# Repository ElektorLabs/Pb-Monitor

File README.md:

# Pb-Monitor

Pb-Monitor is a project developed by ElektorLabs aimed at monitoring lead-acid batteries. This repository contains both hardware schematics and firmware source code to facilitate the monitoring process.

## Features

- **Hardware Design**: Detailed schematics and design files for building the Pb-Monitor hardware.
- **Firmware**: Source code for the microcontroller to interface with the hardware and perform monitoring tasks.

## Repository Structure

- **hardware/**: Contains all hardware design files and schematics.
- **src/PbMonitor/**: Contains the firmware source code for the Pb-Monitor.

## Getting Started

To get started with Pb-Monitor:

1. **Clone the Repository**:
   ```bash
   git clone https://github.com/ElektorLabs/Pb-Monitor.git
   ```
2. **Explore the Hardware Design**:
   - Navigate to the `hardware/` directory to find schematics and design files.
3. **Build the Firmware**:
   - Navigate to the `src/PbMonitor/` directory.
   - Follow the build instructions provided in the source code to compile and upload the firmware to your microcontroller.

## License

This project is licensed under the GNU General Public License v3.0. For more details, refer to the [LICENSE](https://github.com/ElektorLabs/Pb-Monitor/blob/main/LICENSE) file.

## Contributing

Contributions are welcome! If you have suggestions or improvements, feel free to open an issue or submit a pull request.

## Contact

For more information or support, please contact ElektorLabs through their [GitHub profile](https://github.com/ElektorLabs).

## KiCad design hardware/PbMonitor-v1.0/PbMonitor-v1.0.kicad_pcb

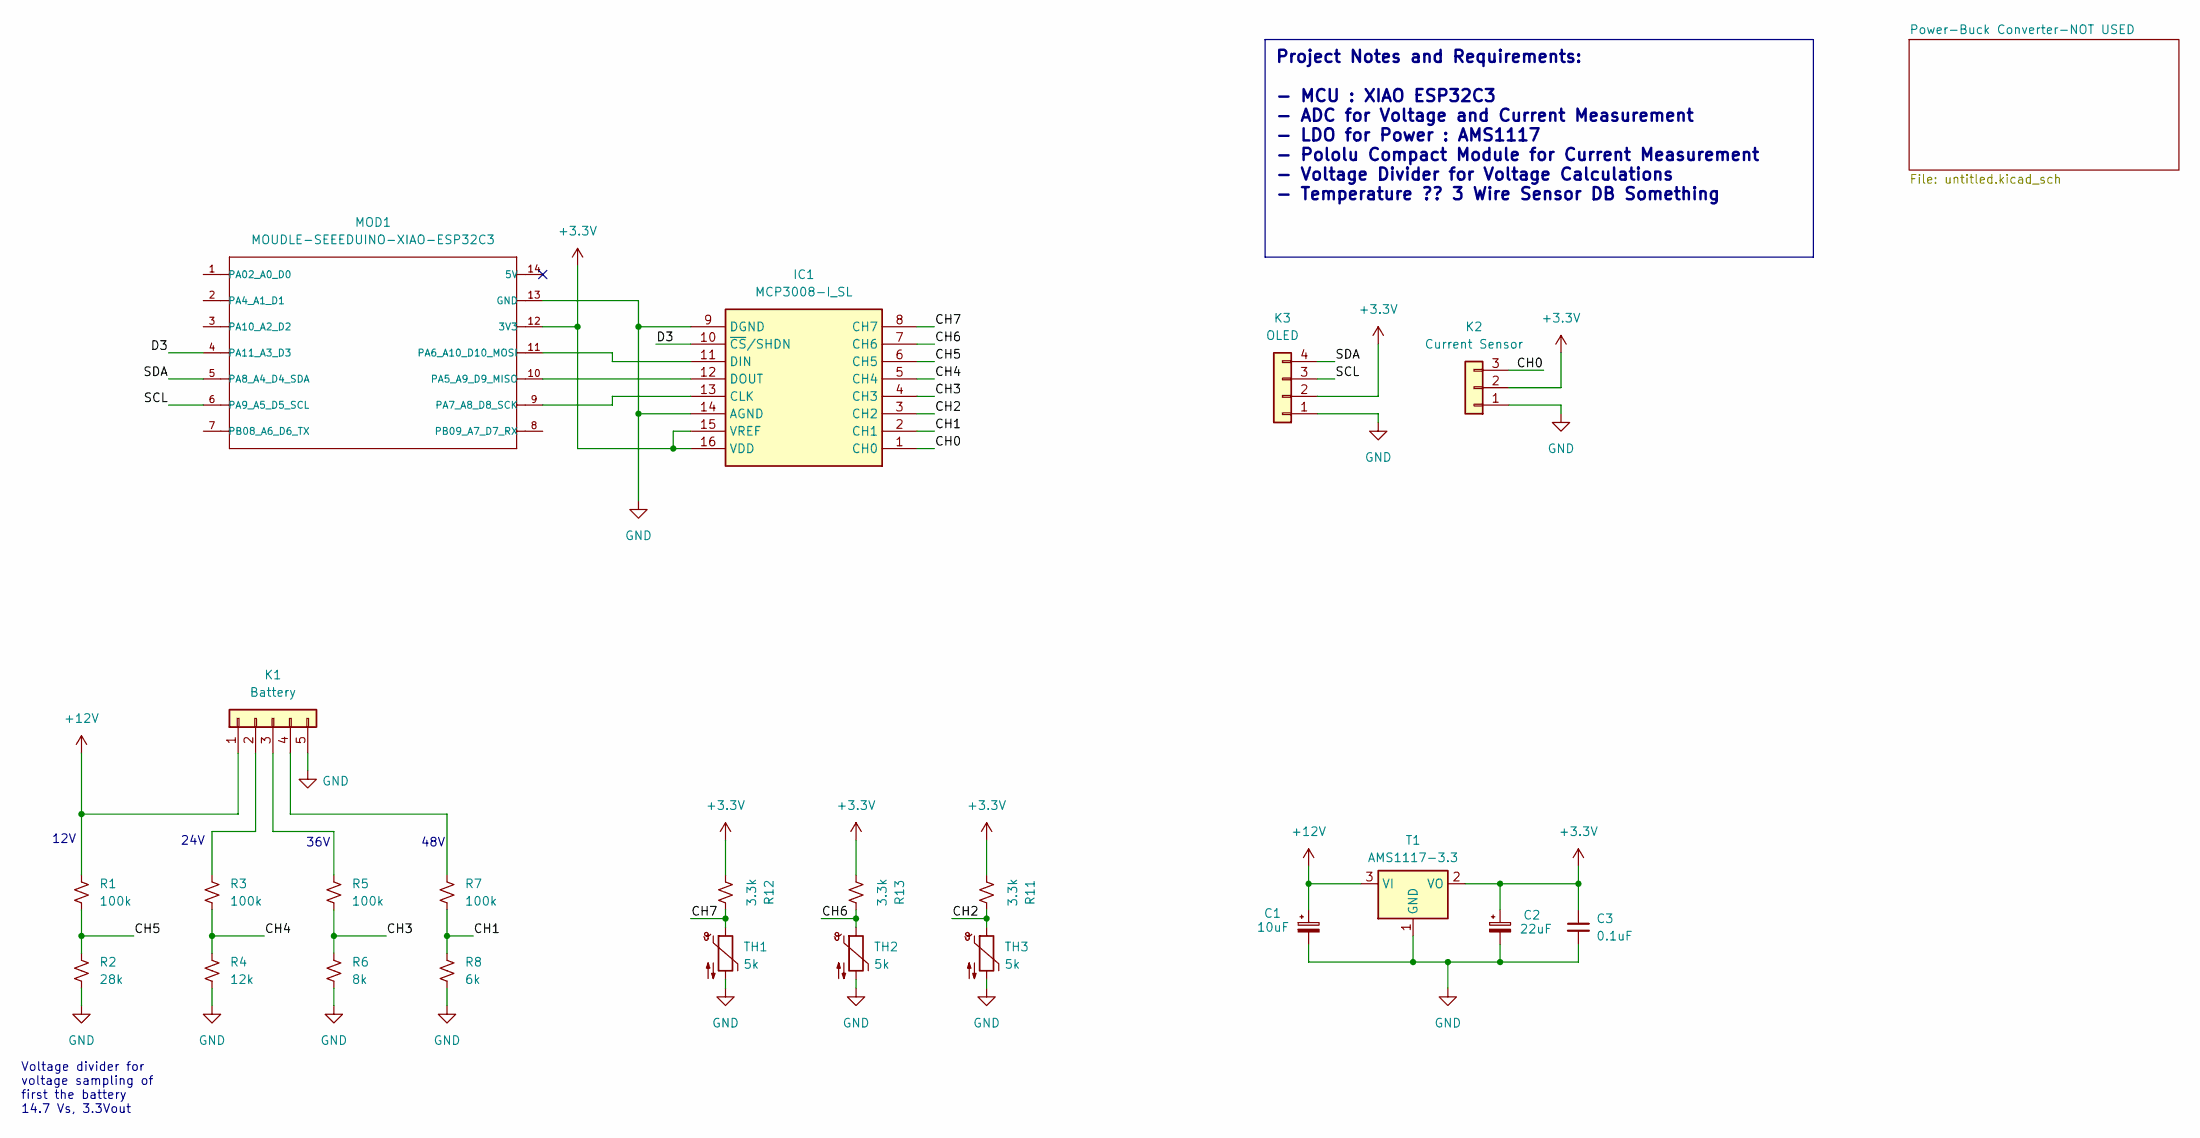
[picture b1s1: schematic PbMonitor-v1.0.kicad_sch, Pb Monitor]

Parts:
C1: 10uF; CP_Radial_D4.0mm_P1.50mm
C2: 22uF; CP_Radial_D4.0mm_P1.50mm
C3: 0.1uF; C_0805_2012Metric_Pad1.18x1.45mm_HandSolder
IC1: MCP3008-I_SL; SOIC127P600X175-16N; Manufacturer_Part_Number MCP3008-I/SL
K1: Battery; TerminalBlock_Xinya_XY308-2.54-5P_1x05_P2.54mm_Horizontal
K2: Current Sensor; PinHeader_1x03_P2.54mm_Vertical
K3: OLED; PinHeader_1x04_P2.54mm_Vertical
MOD1: MOUDLE-SEEEDUINO-XIAO-ESP32C3; XIAO-ESP32C3-DIP
R1, R3, R5, R7: 100k; R_Axial_DIN0204_L3.6mm_D1.6mm_P2.54mm_Vertical
R2: 28k; R_Axial_DIN0204_L3.6mm_D1.6mm_P2.54mm_Vertical
R4: 12k; R_Axial_DIN0204_L3.6mm_D1.6mm_P2.54mm_Vertical
R6: 8k; R_Axial_DIN0204_L3.6mm_D1.6mm_P2.54mm_Vertical
R8: 6k; R_Axial_DIN0204_L3.6mm_D1.6mm_P2.54mm_Vertical
R11, R12, R13: 3.3k; R_Axial_DIN0204_L3.6mm_D1.6mm_P2.54mm_Vertical
T1: AMS1117-3.3; SOT-223-3_TabPin2
TH1, TH2: 5k; JST_XH_B2B-XH-A_1x02_P2.50mm_Vertical
TH3: 5k; R_Axial_DIN0204_L3.6mm_D1.6mm_P2.54mm_Vertical

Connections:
+3.3V: C2.1, C3.1, IC1.15 (VREF), IC1.16 (VDD), K2.2, K3.2, MOD1.12 (3V3), R11.1, R12.1, R13.1, T1.2 (VO)
+12V: C1.1, K1.1, R1.1, T1.3 (VI)
/CH0: IC1.1 (CH0), K2.3
/CH1: IC1.2 (CH1), R7.2, R8.1
/CH2: IC1.3 (CH2), R11.2, TH3.1
/CH3: IC1.4 (CH3), R5.2, R6.1
/CH4: IC1.5 (CH4), R3.2, R4.1
/CH5: IC1.6 (CH5), R1.2, R2.1
/CH6: IC1.7 (CH6), R13.2, TH2.1
/CH7: IC1.8 (CH7), R12.2, TH1.1
/D3: IC1.10 (~CS/SHDN), MOD1.4 (PA11_A3_D3)
/SCL: K3.3, MOD1.6 (PA9_A5_D5_SCL)
/SDA: K3.4, MOD1.5 (PA8_A4_D4_SDA)
GND: C1.2, C2.2, C3.2, IC1.9 (DGND), IC1.14 (AGND), K1.5, K2.1, K3.1, MOD1.13 (GND), R2.2, R4.2, R6.2, R8.2, T1.1 (GND), TH1.2, TH2.2, TH3.2
unnamed: IC1.13 (CLK), MOD1.9 (PA7_A8_D8_SCK)
unnamed: IC1.11 (DIN), MOD1.11 (PA6_A10_D10_MOSI)
unnamed: IC1.12 (DOUT), MOD1.10 (PA5_A9_D9_MISO)
unnamed: K1.2, R3.1
unnamed: K1.3, R5.1
unnamed: K1.4, R7.1

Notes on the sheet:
Project Notes and Requirements: - MCU : XIAO ESP32C3 - ADC for Voltage and Current Measurement - LDO for Power : AMS1117 - Pololu Compact Module for Current Measurement - Voltage Divider for Voltage Calculations - Temperature ?? 3 Wire Sensor DB Something
36V
48V
Voltage divider for voltage sampling of first the battery 14.7 Vs, 3.3Vout
24V
12V

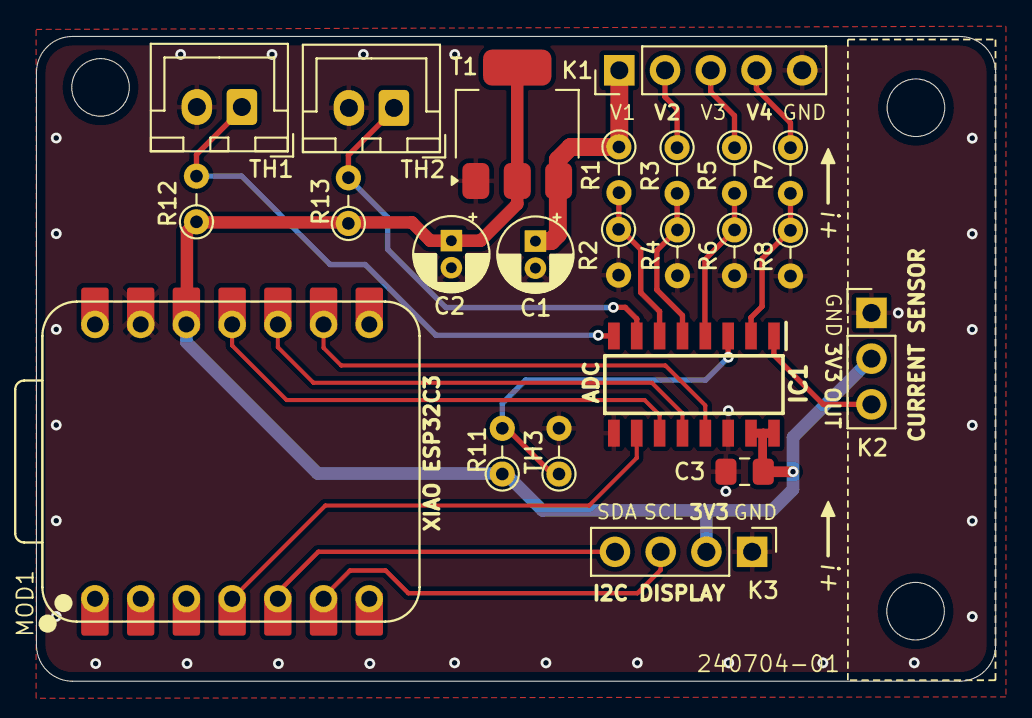
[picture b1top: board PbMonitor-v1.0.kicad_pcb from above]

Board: 2 copper layers, 53.3 x 35.8 mm, 23 parts (0 on the bottom side), 20 nets.

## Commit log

2025-02-03 added files
